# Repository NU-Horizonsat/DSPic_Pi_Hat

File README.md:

# DSPic_Pi_Hat
A Raspberry Pi hat with a DSPic and USB.

To-do list:

## schematic

- [x] USB
- [x] UART chip
- [x] Verify chip selected 
- [ ] Wire DSPic 
    - [x] Wire dubug port
    - [ ] 1n4148 to MCLR?
    - [x] Add oscillator
    - [ ] Check oscillator
    - [x] Wire ADC pins
    - [ ] Check ADC connections
    - [x] Wire PWM pins
    - [x] ~~Wire i2c~~
        - [x] might not even need that (dont need it)
    - [x] rework connectors
    - [x] Dip switches
    - [x] Status LEDs
- [x] Wire to Pi GPIO
    - [x] Power pins
    - [x] Pi to DSPic
    - [x] Screen connectors
    - [x] Status LEDs
- [x] Add ICSP header
    - [ ] Second header for slave core?
- [x] Add connectors for coil drivers
- [ ] Add chip protection
    - [x] Add linear regulator
    - [x] ~~I2C protection~~
    - [x] PWM protection
    - [x] ADC protection
    - [x] Check to make sure the ESD would work
- [x] Find polyfuse to use
- [x] Find capacitor value for C5
- [x] Find crystal
- [x] Find inductor 
- [x] Finalize resistor and led paring 
- [x] Add connector for other PSU

## PCB
- [ ] Test points
- [ ] Add pcb art
- [x] Assign all footprints
- [x] Proper edge cuts for hat
- [x] Grounded screw holes
- [ ] Check footprints
- [x] Connectors and ESD
- [x] USB c and power
- [x] UART
- [x] DSPic

## Parts to order for hand soldering

| Part  | Number | Link |
| ------------- | ------------- | ------------- |
| Crystal  | 1  | https://www.digikey.com/en/products/detail/kyocera-avx/KC2520Z100-000C15XXK/11610165 |
| Inductor  | 1 | https://www.digikey.com/en/products/detail/delta-electronics-components/0805CS-621EGTS/9763907 |
| Amp Connector | 3 | https://www.digikey.com/en/products/detail/molex/5015680807/1531491 | 
| External Power | 1 | https://www.digikey.com/en/products/detail/molex/5015680207/1531485 | 
| Qwiic | 1 | https://www.digikey.com/short/mfth8vvv |
| Raspi Header | 1 | https://www.digikey.com/en/products/detail/sullins-connector-solutions/SFH11-PBPC-D20-ST-BK/1990093 |
| Programming header | 1 | https://www.digikey.com/en/products/detail/samtec-inc/TD-103-T-A/1105555 | 
| Jumper | 1 | https://www.digikey.com/en/products/detail/mill-max-manufacturing-corp/342-10-102-00-591000/4455936 |
| Fuse | 1 | https://www.digikey.com/en/products/detail/littelfuse-inc/1210L500-12SLWR/12807041 |
| Dip switches | 1 | https://www.digikey.com/en/products/detail/cts-electrocomponents/208-8/20795 |

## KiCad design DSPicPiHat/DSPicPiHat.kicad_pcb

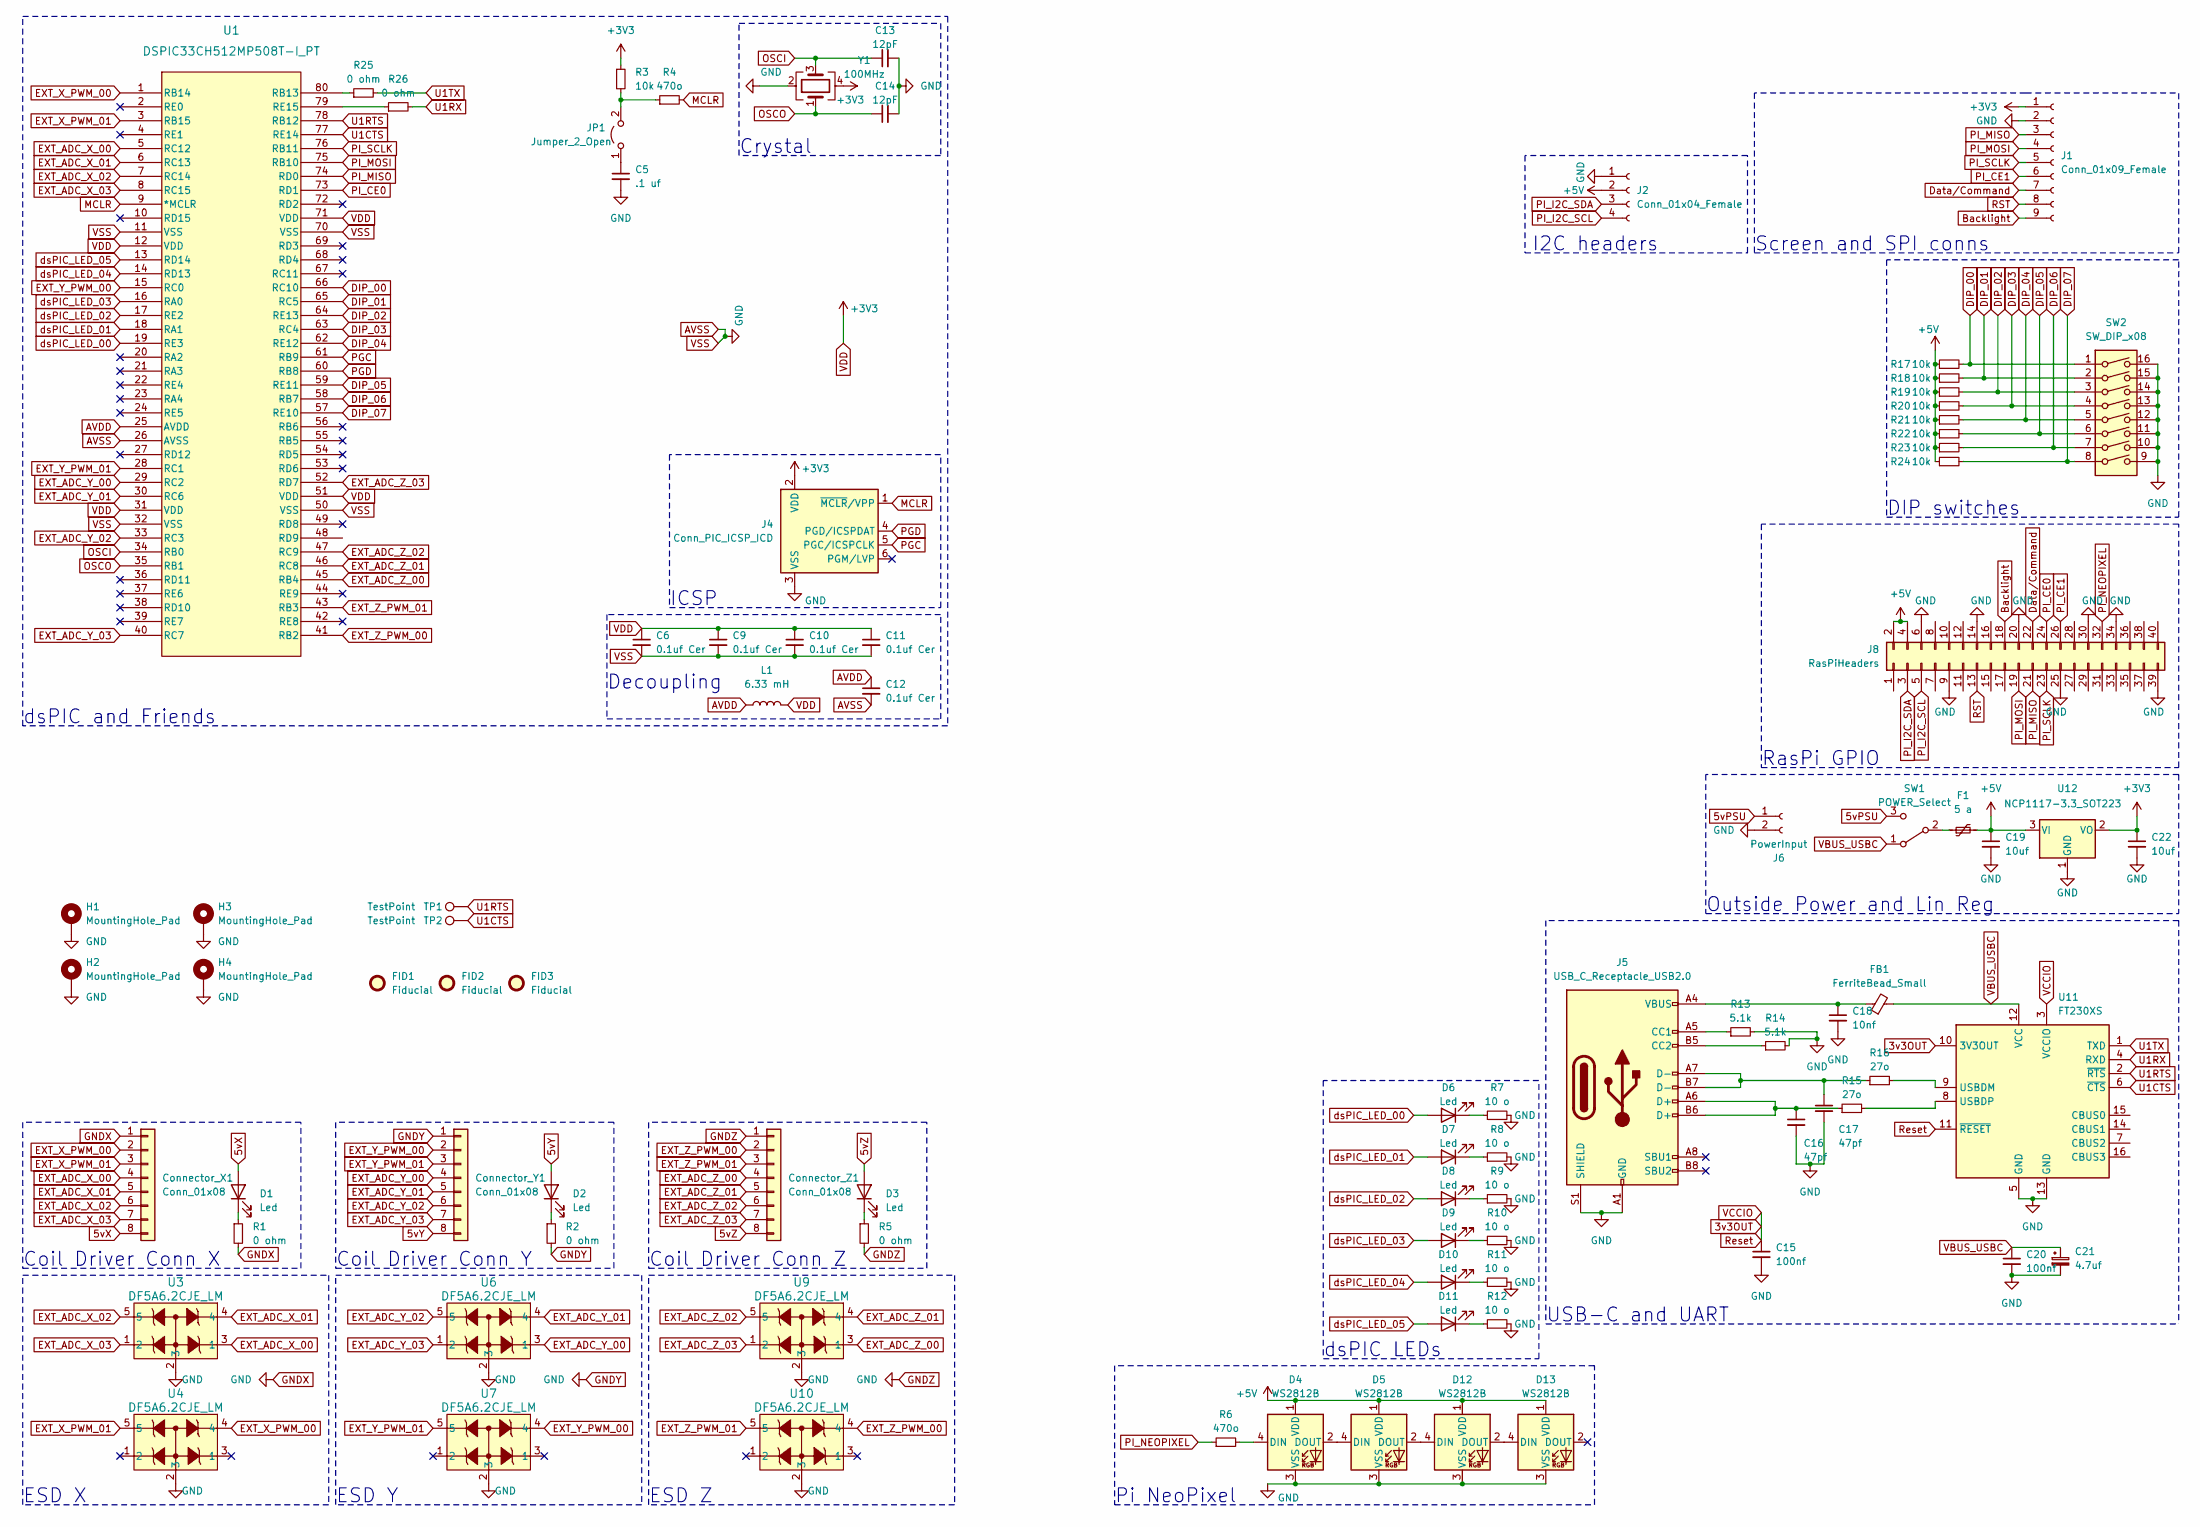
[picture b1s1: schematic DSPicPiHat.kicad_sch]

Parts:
C5: .1 uf; C_0805_2012Metric
C6, C9, C10, C11, C12: 0.1uf Cer; C_0805_2012Metric
C13, C14: 12pF; C_0603_1608Metric
C15, C20: 100nf; C_0805_2012Metric
C16, C17: 47pf; C_0805_2012Metric
C18: 10nf; C_0805_2012Metric
C19, C22: 10uf; C_0805_2012Metric
C21: 4.7uf; CP_Elec_4x5.4
Connector_X1: Conn_01x08; Molex_Pico-Clasp_202396-0807_1x08-1MP_P1.00mm_Horizontal
Connector_Y1: Conn_01x08; Molex_Pico-Clasp_202396-0807_1x08-1MP_P1.00mm_Horizontal
Connector_Z1: Conn_01x08; Molex_Pico-Clasp_202396-0807_1x08-1MP_P1.00mm_Horizontal
D1, D2, D3, D6, D7, D8, D9, D10, D11: Led; LED_0805_2012Metric
D4, D5, D12, D13: WS2812B; LED_WS2812B-2020_PLCC4_2.0x2.0mm
F1: 5 a; Fuse_1210_3225Metric
FB1: FerriteBead_Small; R_1206_3216Metric
FID1, FID2, FID3: Fiducial; Fiducial_1mm_Mask2mm
H1, H2, H3, H4: MountingHole_Pad; MountingHole_2.7mm_M2.5_DIN965_Pad
J1: Conn_01x09_Female; PinHeader_1x09_P2.54mm_Vertical
J2: Conn_01x04_Female; JST_SH_BM04B-SRSS-TB_1x04-1MP_P1.00mm_Vertical
J4: Conn_PIC_ICSP_ICD; PinHeader_2x03_P2.54mm_Vertical
J5: USB_C_Receptacle_USB2.0; USB_C_Receptacle_HRO_TYPE-C-31-M-12
J6: PowerInput; Molex_Pico-Clasp_202396-0207_1x02-1MP_P1.00mm_Horizontal
J8: RasPiHeaders; PinSocket_2x20_P2.54mm_Vertical
JP1: Jumper_2_Open; PinHeader_1x02_P2.54mm_Vertical
L1: 6.33 mH; L_0805_2012Metric
R1, R2, R5, R25, R26: 0 ohm; R_0805_2012Metric
R3, R17, R18, R19, R20, R21, R22, R23, R24: 10k; R_0805_2012Metric
R4, R6: 470o; R_0805_2012Metric
R7, R8, R9, R10, R11, R12: 10 o; R_0805_2012Metric
R13, R14: 5.1k; R_0805_2012Metric
R15, R16: 27o; R_0805_2012Metric
SW1: POWER_Select; SW_SPDT_PCM12
SW2: SW_DIP_x08; SW_DIP_SPSTx08_Slide_9.78x22.5mm_W7.62mm_P2.54mm
TP1, TP2: TestPoint; TestPoint_Pad_D1.0mm
U1: DSPIC33CH512MP508T-I_PT; TQFP-80_12x12mm_P0.5mm
U3, U4, U6, U7, U9, U10: DF5A6.2CJE_LM; SOT-553
U11: FT230XS; SSOP-16_3.9x4.9mm_P0.635mm
U12: NCP1117-3.3_SOT223; SOT-223-3_TabPin2
Y1: 100MHz; Crystal_SMD_2520-4Pin_2.5x2.0mm

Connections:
3v3OUT: C15.1, U11.3 (VCCIO), U11.10 (3V3OUT), U11.11 (~RESET)
5vPSU: J6.1, SW1.3 (C)
5vX: Connector_X1.8, D1.2 (A)
5vY: Connector_Y1.8, D2.2 (A)
5vZ: Connector_Z1.8, D3.2 (A)
+5V: C19.1, D4.1 (VDD), D5.1 (VDD), D12.1 (VDD), D13.1 (VDD), F1.2, J2.2, J8.2, J8.4, R17.1, R18.1, R19.1, R20.1, R21.1, R22.1, R23.1, R24.1, U12.3 (VI)
AVDD: C12.1, L1.1, U1.25 (AVDD)
AVSS: C5.2, C6.2, C9.2, C10.2, C11.2, C12.2, C13.2, C14.2, C15.2, C16.2, C17.2, C18.2, C19.2, C20.2, C21.2, C22.2, Connector_X1.1, Connector_Y1.1, Connector_Z1.1, D4.3 (VSS), D5.3 (VSS), D12.3 (VSS), D13.3 (VSS), H1.1, H2.1, H3.1, H4.1, J1.2, J2.1, J4.3 (VSS), J5.A1 (GND), J5.A12 (GND), J5.B1 (GND), J5.B12 (GND), J5.S1 (SHIELD), J6.2, J8.6, J8.9, J8.14, J8.20, J8.25, J8.30, J8.34, J8.39, R1.2, R2.2, R5.2, R7.2, R8.2, R9.2, R10.2, R11.2, R12.2, R13.2, R14.2, SW2.9, SW2.10, SW2.11, SW2.12, SW2.13, SW2.14, SW2.15, SW2.16, U1.11 (VSS), U1.26 (AVSS), U1.32 (VSS), U1.50 (VSS), U1.70 (VSS), U3.2 (3), U4.2 (3), U6.2 (3), U7.2 (3), U9.2 (3), U10.2 (3), U11.5 (GND), U11.13 (GND), U12.1 (GND), Y1.2
Backlight: J1.9, J8.18
DIP_00: R17.2, SW2.1, U1.66 (RC10)
DIP_01: R18.2, SW2.2, U1.65 (RC5)
DIP_02: R19.2, SW2.3, U1.64 (RE13)
DIP_03: R20.2, SW2.4, U1.63 (RC4)
DIP_04: R21.2, SW2.5, U1.62 (RE12)
DIP_05: R22.2, SW2.6, U1.59 (RE11)
DIP_06: R23.2, SW2.7, U1.58 (RB7)
DIP_07: R24.2, SW2.8, U1.57 (RE10)
Data/Command: J1.7, J8.22
EXT_ADC_X_00: Connector_X1.4, U1.5 (RC12), U3.3 (1)
EXT_ADC_X_01: Connector_X1.5, U1.6 (RC13), U3.4
EXT_ADC_X_02: Connector_X1.6, U1.7 (RC14), U3.5
EXT_ADC_X_03: Connector_X1.7, U1.8 (RC15), U3.1 (2)
EXT_ADC_Y_00: Connector_Y1.4, U1.29 (RC2), U6.3 (1)
EXT_ADC_Y_01: Connector_Y1.5, U1.30 (RC6), U6.4
EXT_ADC_Y_02: Connector_Y1.6, U1.33 (RC3), U6.5
EXT_ADC_Y_03: Connector_Y1.7, U1.40 (RC7), U6.1 (2)
EXT_ADC_Z_00: Connector_Z1.4, U1.45 (RB4), U9.3 (1)
EXT_ADC_Z_01: Connector_Z1.5, U1.46 (RC8), U9.4
EXT_ADC_Z_02: Connector_Z1.6, U1.47 (RC9), U9.5
EXT_ADC_Z_03: Connector_Z1.7, U1.52 (RD7), U9.1 (2)
EXT_X_PWM_00: Connector_X1.2, U1.1 (RB14), U4.4
EXT_X_PWM_01: Connector_X1.3, U1.3 (RB15), U4.5
EXT_Y_PWM_00: Connector_Y1.2, U1.15 (RC0), U7.4
EXT_Y_PWM_01: Connector_Y1.3, U1.28 (RC1), U7.5
EXT_Z_PWM_00: Connector_Z1.2, U1.41 (RB2), U10.4
EXT_Z_PWM_01: Connector_Z1.3, U1.43 (RB3), U10.5
MCLR: J4.1 (~MCLR/VPP), R4.2, U1.9 (*MCLR)
unnamed: C16.1, J5.A6 (D+), J5.B6 (D+), R15.1
unnamed: C17.1, J5.A7 (D-), J5.B7 (D-), R16.1
unnamed: C18.1, FB1.1, J5.A4 (VBUS), J5.A9 (VBUS), J5.B4 (VBUS), J5.B9 (VBUS)
unnamed: D1.1 (K), R1.1
unnamed: D2.1 (K), R2.1
unnamed: D3.1 (K), R5.1
unnamed: D4.4 (DIN), R6.2
unnamed: D4.2 (DOUT), D5.4 (DIN)
unnamed: D6.1 (K), R7.1
unnamed: D7.1 (K), R8.1
unnamed: D8.1 (K), R9.1
unnamed: D9.1 (K), R10.1
unnamed: D10.1 (K), R11.1
unnamed: D11.1 (K), R12.1
unnamed: D5.2 (DOUT), D12.4 (DIN)
unnamed: D12.2 (DOUT), D13.4 (DIN)
unnamed: J5.A5 (CC1), R13.1
unnamed: J5.B5 (CC2), R14.1
unnamed: C5.1, JP1.1 (A)
unnamed: JP1.2 (B), R3.2, R4.1
unnamed: F1.1, SW1.2 (B)
unnamed: R25.1, U1.80 (RB13)
unnamed: R26.1, U1.79 (RE15)
unnamed: R16.2, U11.9 (USBDM)
unnamed: R15.2, U11.8 (USBDP)
OSCI: C13.1, U1.34 (RB0), Y1.3
OSCO: C14.1, U1.35 (RB1), Y1.1
PGC: J4.5 (PGC/ICSPCLK), U1.61 (RB9)
PGD: J4.4 (PGD/ICSPDAT), U1.60 (RB8)
PI_CE0: J8.24, U1.73 (RD1)
PI_CE1: J1.6, J8.26
PI_I2C_SCL: J2.4, J8.5
PI_I2C_SDA: J2.3, J8.3
PI_MISO: J1.3, J8.21, U1.74 (RD0)
PI_MOSI: J1.4, J8.19, U1.75 (RB10)
PI_NEOPIXEL: J8.32, R6.1
PI_SCLK: J1.5, J8.23, U1.76 (RB11)
RST: J1.8, J8.13
U1CTS: TP2.1, U1.77 (RE14), U11.6 (~CTS)
U1RTS: TP1.1, U1.78 (RB12), U11.2 (~RTS)
U1RX: R26.2, U11.4 (RXD)
U1TX: R25.2, U11.1 (TXD)
VBUS_USBC: C20.1, C21.1, FB1.2, SW1.1 (A), U11.12 (VCC)
VDD: C6.1, C9.1, C10.1, C11.1, C22.1, J1.1, J4.2 (VDD), L1.2, R3.1, U1.12 (VDD), U1.31 (VDD), U1.51 (VDD), U1.71 (VDD), U12.2 (VO), Y1.4
dsPIC_LED_00: D6.2 (A), U1.19 (RE3)
dsPIC_LED_01: D7.2 (A), U1.18 (RA1)
dsPIC_LED_02: D8.2 (A), U1.17 (RE2)
dsPIC_LED_03: D9.2 (A), U1.16 (RA0)
dsPIC_LED_04: D10.2 (A), U1.14 (RD13)
dsPIC_LED_05: D11.2 (A), U1.13 (RD14)

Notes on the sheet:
Decoupling
USB-C and UART
Pi NeoPixel
ICSP
dsPIC LEDs
RasPi GPIO
Screen and SPI conns
Outside Power and Lin Reg
I2C headers
ESD Z
ESD Y
dsPIC and Friends
Coil Driver Conn Y
DIP switches
Crystal
Coil Driver Conn Z
Coil Driver Conn X
ESD X

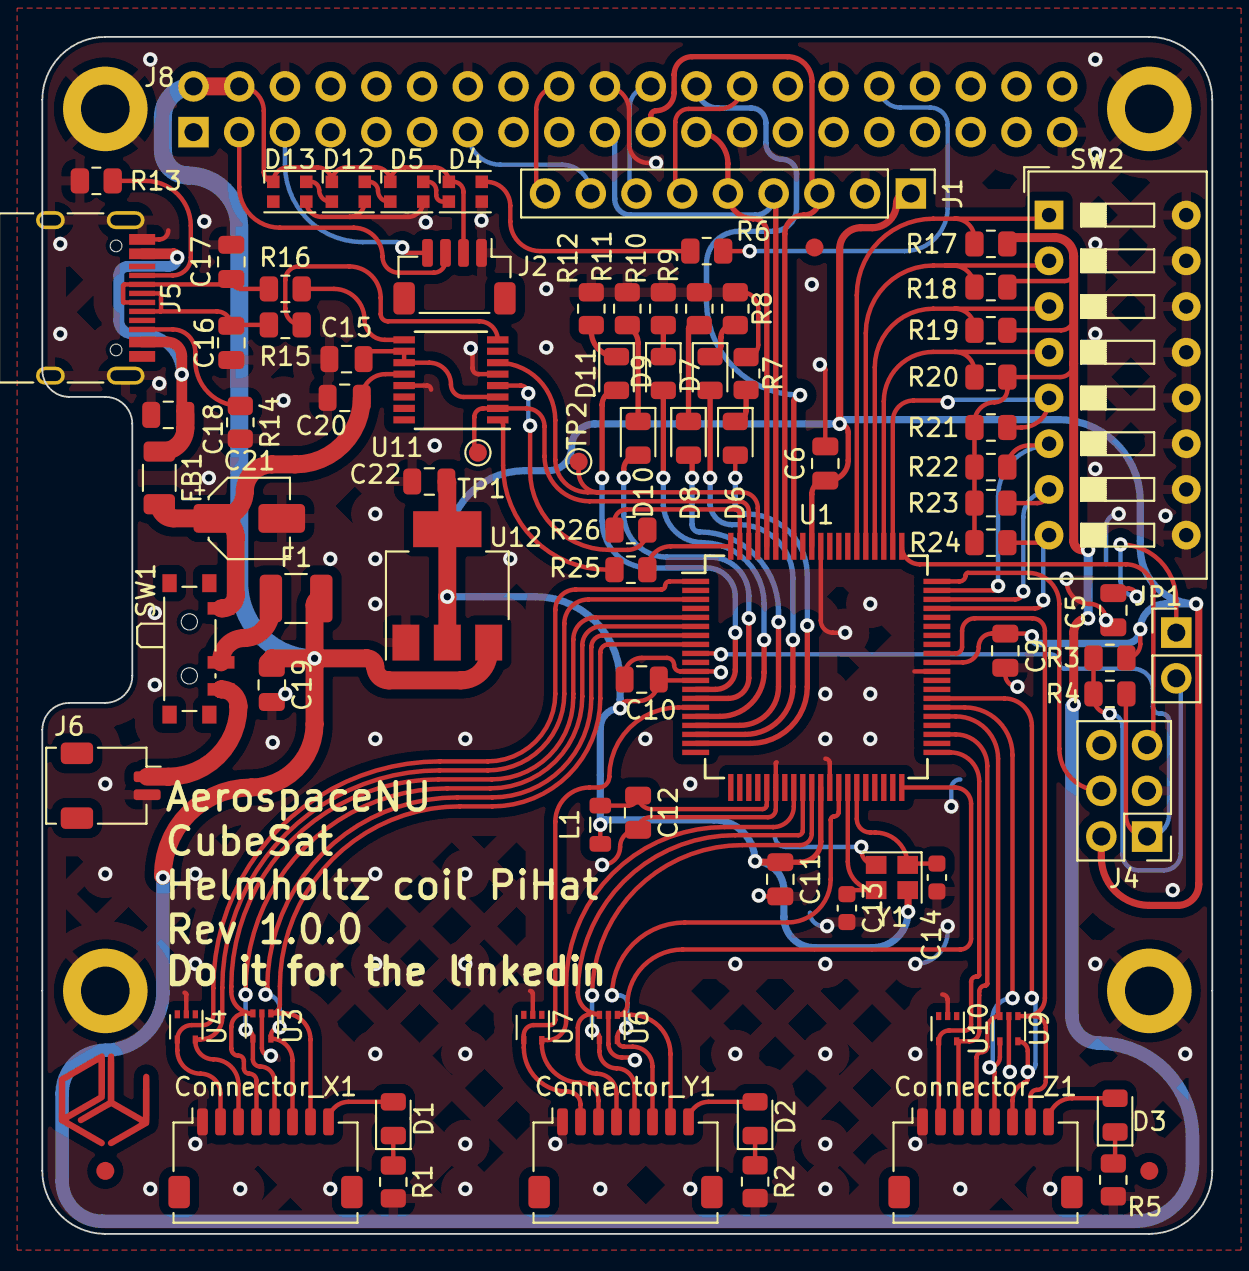
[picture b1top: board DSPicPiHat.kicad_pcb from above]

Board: 2 copper layers, 65.0 x 66.5 mm, 89 parts (1 on the bottom side), 87 nets.

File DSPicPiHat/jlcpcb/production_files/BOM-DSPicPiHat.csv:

Comment,Designator,Footprint,LCSC
NCP1117-3.3_SOT223,U12,SOT-223-3_TabPin2,C146799
47pf,"C16,C17",C_0805_2012Metric,C14857
10uf,"C19,C22",C_0805_2012Metric,C15850
10nf,C18,C_0805_2012Metric,C1710
10k,"R17,R18,R19,R20,R21,R22,R23,R24,R3",R_0805_2012Metric,C17414
10 o,"R10,R11,R12,R7,R8,R9",R_0805_2012Metric,C17415
470o,"R4,R6",R_0805_2012Metric,C17710
12pF,"C13,C14",C_0603_1608Metric,C1792
4.7uf,C21,CP_Elec_4x5.4,C213488
POWER_Select,SW1,SW_SPDT_PCM12,C221841
DF5A6.2CJE_LM,"U10,U3,U4,U6,U7,U9",SOT-553,C2762689
5.1k,"R13,R14",R_0805_2012Metric,C27834
0.1uf Cer,"C10,C11,C12,C15,C20,C5,C6,C9",C_0805_2012Metric,C28233
USB_C_Receptacle_USB2.0,J5,USB_C_Receptacle_HRO_TYPE-C-31-M-12,C2927038
FerriteBead_Small,FB1,R_1206_3216Metric,C317622
Led,"D1,D10,D11,D2,D3,D6,D7,D8,D9",LED_0805_2012Metric,C34499
27o,"R15,R16",R_0805_2012Metric,C365278
WS2812B,"D12,D13,D4,D5",LED_WS2812B-2020_PLCC4_2.0x2.0mm,C4154877
FT230XS,U11,SSOP-16_3.9x4.9mm_P0.635mm,C69082
Conn_01x04_Female,J2,JST_SH_BM04B-SRSS-TB_1x04-1MP_P1.00mm_Vertical,
Fiducial,FID1,Fiducial_1mm_Mask2mm,
0 ohm,R2,R_0805_2012Metric,
0 ohm,R5,R_0805_2012Metric,
0 ohm,R1,R_0805_2012Metric,
Jumper_2_Open,JP1,PinHeader_1x02_P2.54mm_Vertical,
Conn_PIC_ICSP_ICD,J4,PinHeader_2x03_P2.54mm_Vertical,
SW_DIP_x08,SW2,SW_DIP_SPSTx08_Slide_9.78x22.5mm_W7.62mm_P2.54mm,
MountingHole_Pad,H4,MountingHole_2.7mm_M2.5_DIN965_Pad,
TestPoint,TP1,TestPoint_Pad_D1.0mm,
0 ohm,R25,R_0805_2012Metric,
0 ohm,R26,R_0805_2012Metric,
TestPoint,TP2,TestPoint_Pad_D1.0mm,
100MHz,Y1,Crystal_SMD_2520-4Pin_2.5x2.0mm,
Fiducial,FID3,Fiducial_1mm_Mask2mm,
MountingHole_Pad,H1,MountingHole_2.7mm_M2.5_DIN965_Pad,
DSPIC33CH512MP508T-I_PT,U1,TQFP-80_12x12mm_P0.5mm,
Conn_01x08,Connector_X1,Molex_Pico-Clasp_202396-0807_1x08-1MP_P1.00mm_Horizontal,
6.33 mH,L1,L_0805_2012Metric,
Fiducial,FID2,Fiducial_1mm_Mask2mm,
Conn_01x08,Connector_Y1,Molex_Pico-Clasp_202396-0807_1x08-1MP_P1.00mm_Horizontal,
Conn_01x08,Connector_Z1,Molex_Pico-Clasp_202396-0807_1x08-1MP_P1.00mm_Horizontal,
MountingHole_Pad,H2,MountingHole_2.7mm_M2.5_DIN965_Pad,
PowerInput,J6,Molex_Pico-Clasp_202396-0207_1x02-1MP_P1.00mm_Horizontal,
5 a,F1,Fuse_1210_3225Metric,
Conn_01x09_Female,J1,PinHeader_1x09_P2.54mm_Vertical,
MountingHole_Pad,H3,MountingHole_2.7mm_M2.5_DIN965_Pad,
RasPiHeaders,J8,PinSocket_2x20_P2.54mm_Vertical,

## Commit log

2024-03-01 Started work on schematic
    added the correct DSPic (i think), added usb, headers, and power spdt. Added gitignore file for the backups folder.
2024-03-01 Added USB wiring and UART chip
2024-03-01 added to-do list
2024-03-02 Added linear regulator expanded to-do list
2024-03-02 Added debug port, polyfuse, and organizational changes.
2024-03-02 Added correct dsPIC chip and connected it to parts., added coil driver connector, added tvs diodes.
2024-03-02 Wire ADC to dsPIC, moved things around.
2024-03-02 each axis needs own conn
2024-03-03 more coil driver headers and protection
2024-03-03 added leds to coil connector plugs
2024-03-03 wired up i2c, PWM, and ADC pins from connectors
2024-03-04 dsPIC to Pi, dsPIC dip switches, dspic and Pi LEDs, and spi screen connectors.
2024-03-22 fix connector connections and remove extra ones, switches resistor array for multiple resistors
2024-03-22 start adding pcb footprints, working on pcb outline, and starting routing.
    Also removed resistor array.
2024-03-22 ESD connected to axis connectors.
2024-03-23 Power, USB, and UART
2024-03-23 Connected all the coil driver connectors. Added more footprints.
2024-03-24 PCB mostly routed
2024-03-27 changed connectors and removed i2c lines and i2c isolator.
2024-03-27 added fiducials and slightly moved some things around.
2024-03-29 Adjusting silk screen locations
2024-03-29 Rounded some comers and added more pcb art
2024-03-29 Grounded mounting points
2024-04-02 Fixed pi header connections
2024-04-03 Moved fuse to be after the PSU switch
2024-04-03 oops
2024-04-06 added o ohm resistors based on braincodec's rx tx switcher
2024-04-08 dip_00 was unconnected, working through drc errors and warnings.
2024-04-09 made a few traces slightly thicker
2024-04-09 organized schem
2024-04-10 filling in unkown values and footprints
2024-04-10 removed islands, added more vias, fixed routing, added no connect.
2024-04-10 Added more vias, removed some hanging ground pours, updated drc and fixed any errors.
2024-04-11 made small fixes and finishing touches
2024-04-11 kicad v8!
2024-04-11 started work on selecting parts for pcba
2024-04-12 more basic parts!
2024-04-12 added more parts to bom
2024-04-12 generate production files
2024-04-12 Create LICENSE
2024-04-17 added list of parts needed
2024-04-17 fixed ferrite bead part selection
